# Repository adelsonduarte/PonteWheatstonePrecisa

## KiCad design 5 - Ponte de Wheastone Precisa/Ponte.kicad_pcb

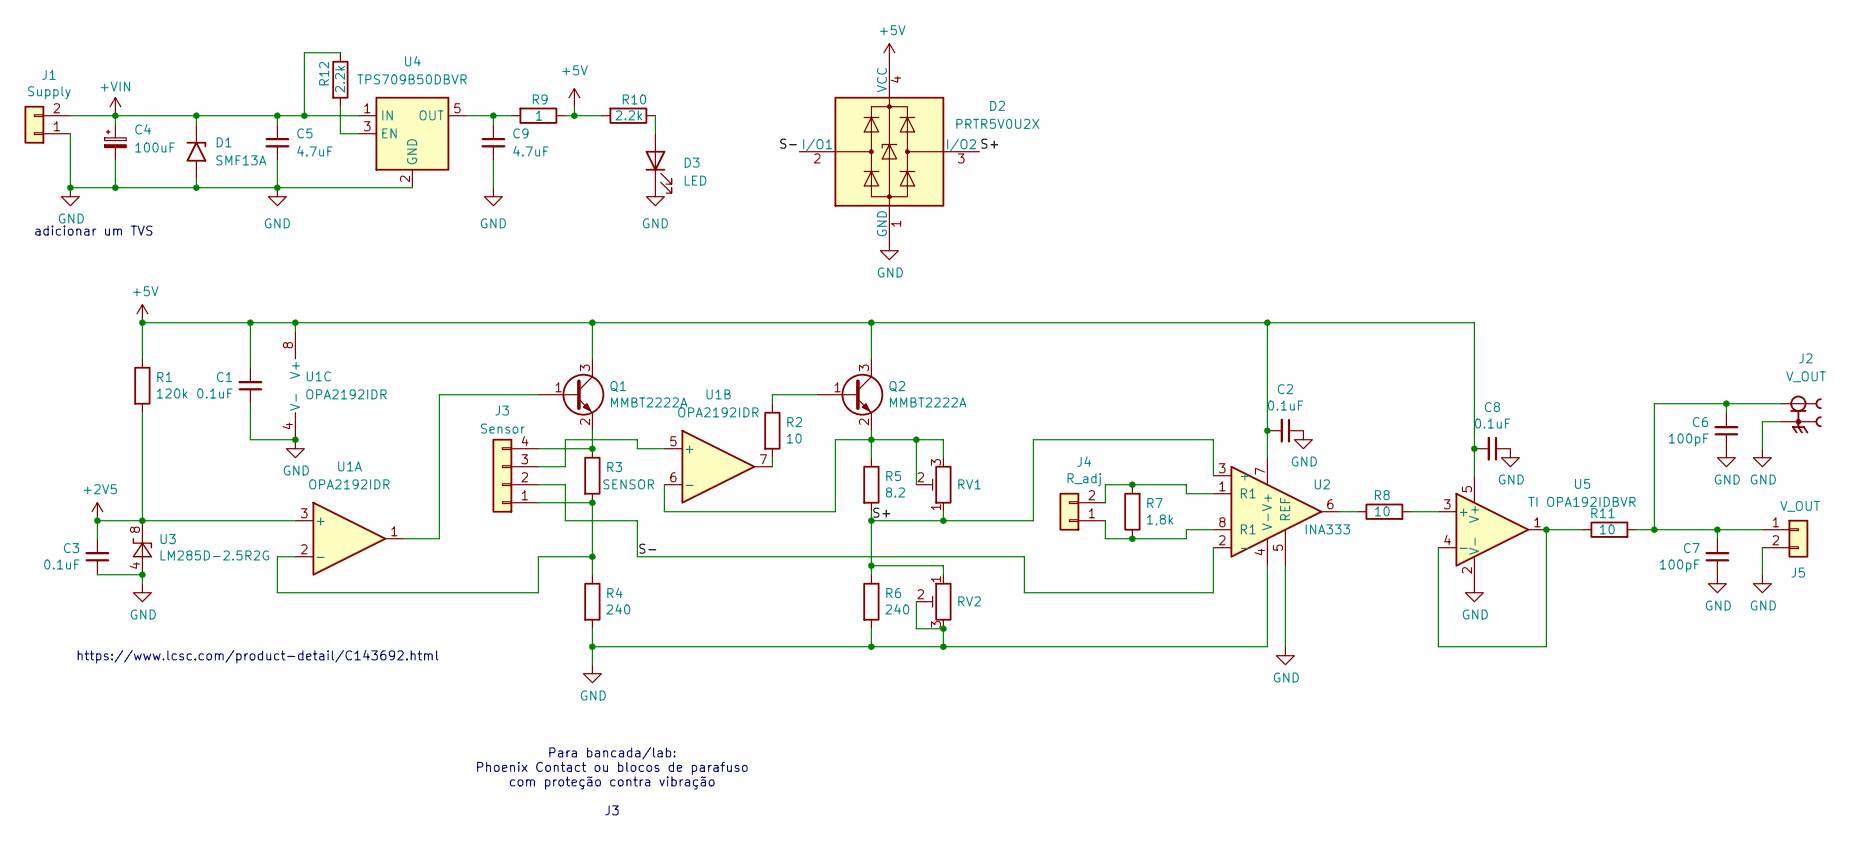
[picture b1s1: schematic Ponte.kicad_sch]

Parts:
C1, C2, C3, C8: 0.1uF; C_0805_2012Metric_Pad1.18x1.45mm_HandSolder; LCSC part # C519980
C4: 100uF; C_Elec_8x6.2; LCSC part # C88744
C5, C9: 4.7uF; C_0805_2012Metric; LCSC part # C107365
C6, C7: 100pF; C_0805_2012Metric_Pad1.18x1.45mm_HandSolder; LCSC part # C182933
D1: SMF13A; D_SOD-123F; LCSC part # C2857274
D2: PRTR5V0U2X; SOT-143; LCSC part # C2827688
D3: LED; LED_0805_2012Metric; LCSC part # C375451
J1: Supply; Molex_KK-254_AE-6410-02A_1x02_P2.54mm_Vertical; LCSC part # C5447965
J2: V_OUT; LINX_CONSMA020.062-G; PARTREV A
J3: Sensor; Molex_KK-254_AE-6410-04A_1x04_P2.54mm_Vertical; LCSC part # C5447965
J4: R_adj; Molex_KK-254_AE-6410-02A_1x02_P2.54mm_Vertical; LCSC part # C5447965
J5: V_OUT; Molex_KK-254_AE-6410-02A_1x02_P2.54mm_Vertical; LCSC part # C5447965
Q1, Q2: MMBT2222A; SOT-23; LCSC part # C82460
R1: 120k; R_0805_2012Metric_Pad1.20x1.40mm_HandSolder; LCSC part # C304119
R2, R8, R11: 10; R_0805_2012Metric_Pad1.20x1.40mm_HandSolder; LCSC part # C217774
R3: SENSOR; R_0805_2012Metric_Pad1.20x1.40mm_HandSolder
R4, R6: 240; R_0805_2012Metric_Pad1.20x1.40mm_HandSolder; LCSC part # C869301
R5: 8.2; R_0805_2012Metric_Pad1.20x1.40mm_HandSolder; LCSC part # C136890
R7: 1,8k; R_0805_2012Metric_Pad1.20x1.40mm_HandSolder; LCSC part # C375519
R9: 1; R_2512_6332Metric_Pad1.40x3.35mm_HandSolder; LCSC part # C4033338
R10, R12: 2.2k; R_0805_2012Metric; LCSC part # C19269962
RV1, RV2: R_POT_TRIM; Potentiometer_Bourns_3296W_Vertical; LCSC part # C58161
U1: OPA2192IDR; SOIC-8_3.9x4.9mm_P1.27mm; LCSC part # C110074
U2: INA333; VSSOP-8_3x3mm_P0.65mm; LCSC part # C19450
U3: LM285D-2.5R2G; SOIC-8_3.9x4.9mm_P1.27mm; LCSC part # C7931
U4: TPS709B50DBVR; SOT-23-5; LCSC part # C2867109
U5: TI OPA192IDBVR; SOT-23-5; LCSC part # C139648

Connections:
+2V5: C3.2, R1.2, U1.3 (+), U3.8 (K)
+5V: C1.2, C2.2, C8.2, D2.4 (VCC), Q1.3 (C), Q2.3 (C), R1.1, R9.1, R10.2, U1.8 (V+), U2.7 (V+), U5.5 (V+)
+VIN: C4.1, C5.1, D1.1 (A1), J1.2, R12.1, U4.1 (IN)
/S+: D2.3 (I/O2), R5.2, R6.1, RV1.1, RV2.1, U2.3 (+)
/S-: D2.2 (I/O1), J3.2, U2.2 (-)
GND: C1.1, C2.1, C3.1, C4.2, C5.2, C6.1, C7.1, C8.1, C9.2, D1.2 (A2), D2.1 (GND), D3.1 (K), J1.1, J2.S1, J5.2, R4.2, R6.2, RV2.2, RV2.3, U1.4 (V-), U2.4 (V-), U2.5 (REF), U3.4 (A), U4.2 (GND), U5.2 (V-)
unnamed: D3.2 (A), R10.1
unnamed: J3.1, R3.2, R4.1, U1.2 (-)
unnamed: J3.3, U1.5 (+)
unnamed: J3.4, Q1.2 (E), R3.1
unnamed: J4.1, R7.1, U2.8 (R1)
unnamed: J4.2, R7.2, U2.1 (R1)
unnamed: C6.2, C7.2, J2.1, J5.1, R11.2
unnamed: Q1.1 (B), U1.1
unnamed: Q2.1 (B), R2.1
unnamed: Q2.2 (E), R5.1, RV1.2, RV1.3, U1.6 (-)
unnamed: R2.2, U1.7
unnamed: R8.1, U2.6
unnamed: R12.2, U4.3 (EN)
unnamed: C9.1, R9.2, U4.5 (OUT)
unnamed: R8.2, U5.3 (+)
unnamed: R11.1, U5.1, U5.4 (-)

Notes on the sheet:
Para bancada/lab: Phoenix Contact ou blocos de parafuso com proteção contra vibração J3
https://www.lcsc.com/product-detail/C143692.html
adicionar um TVS

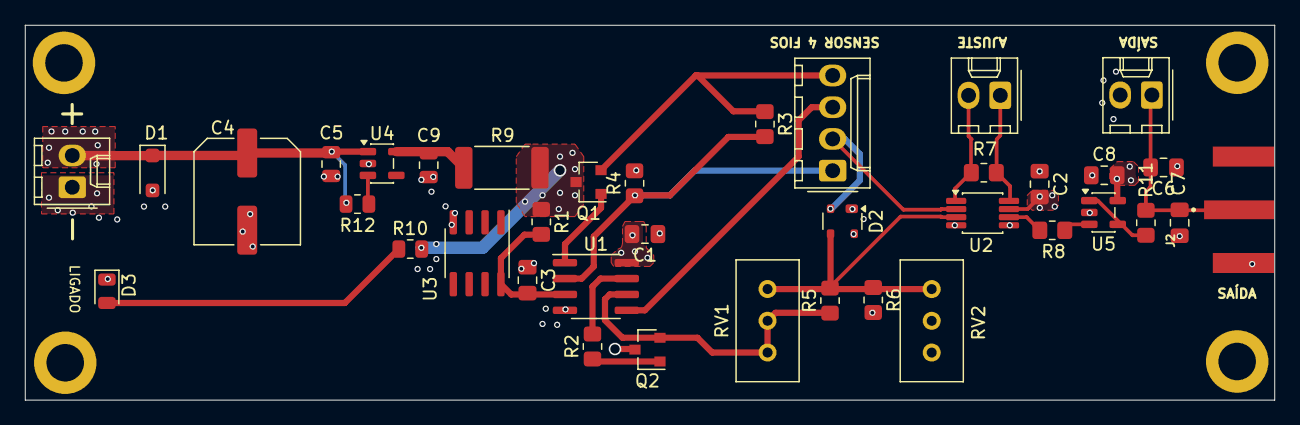
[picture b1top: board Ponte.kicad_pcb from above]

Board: 4 copper layers, 100.0 x 30.0 mm, 38 parts (0 on the bottom side), 22 nets.

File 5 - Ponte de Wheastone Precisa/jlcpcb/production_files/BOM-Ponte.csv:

Comment,Designator,Footprint,LCSC,Quantity
0.1uF,"C1,C2,C3,C8",C_0805_2012Metric_Pad1.18x1.45mm_HandSolder,C519980,4
1,R9,R_2512_6332Metric_Pad1.40x3.35mm_HandSolder,C4033338,1
"1,8k",R7,R_0805_2012Metric_Pad1.20x1.40mm_HandSolder,C375519,1
10,"R11,R2,R8",R_0805_2012Metric_Pad1.20x1.40mm_HandSolder,C217774,3
100pF,"C6,C7",C_0805_2012Metric_Pad1.18x1.45mm_HandSolder,C182933,2
100uF,C4,C_Elec_8x6.2,C88744,1
120k,R1,R_0805_2012Metric_Pad1.20x1.40mm_HandSolder,C304119,1
2.2k,"R10,R12",R_0805_2012Metric,C19269962,2
240,"R4,R6",R_0805_2012Metric_Pad1.20x1.40mm_HandSolder,C869301,2
4.7uF,"C5,C9",C_0805_2012Metric,C107365,2
8.2,R5,R_0805_2012Metric_Pad1.20x1.40mm_HandSolder,C136890,1
INA333,U2,VSSOP-8_3x3mm_P0.65mm,C19450,1
LED,D3,LED_0805_2012Metric,C375451,1
LM285D-2.5R2G,U3,SOIC-8_3.9x4.9mm_P1.27mm,C7931,1
MMBT2222A,"Q1,Q2",SOT-23,C82460,2
OPA2192IDR,U1,SOIC-8_3.9x4.9mm_P1.27mm,C110074,1
PRTR5V0U2X,D2,SOT-143,C2827688,1
R_POT_TRIM,"RV1,RV2",Potentiometer_Bourns_3296W_Vertical,C58161,2
R_adj,J4,Molex_KK-254_AE-6410-02A_1x02_P2.54mm_Vertical,C5447965,1
SMF13A,D1,D_SOD-123F,C2857274,1
Sensor,J3,Molex_KK-254_AE-6410-04A_1x04_P2.54mm_Vertical,C5447965,1
Supply,J1,Molex_KK-254_AE-6410-02A_1x02_P2.54mm_Vertical,C5447965,1
TI OPA192IDBVR,U5,SOT-23-5,C139648,1
TPS709B50DBVR,U4,SOT-23-5,C2867109,1
V_OUT,J5,Molex_KK-254_AE-6410-02A_1x02_P2.54mm_Vertical,C5447965,1
SENSOR,R3,R_0805_2012Metric_Pad1.20x1.40mm_HandSolder,,1
V_OUT,J2,LINX_CONSMA020.062-G,,1

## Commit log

2026-03-06 Esquemático finalizado
2026-03-06 Adicionado sensor 4 fios; PCB_1
2026-03-07 Posicionado e roteado. Restando adicionar vias de GND e guard ring.
2026-03-08 Adicionado silks e furos para suporte. Preço com montagem R04,54
